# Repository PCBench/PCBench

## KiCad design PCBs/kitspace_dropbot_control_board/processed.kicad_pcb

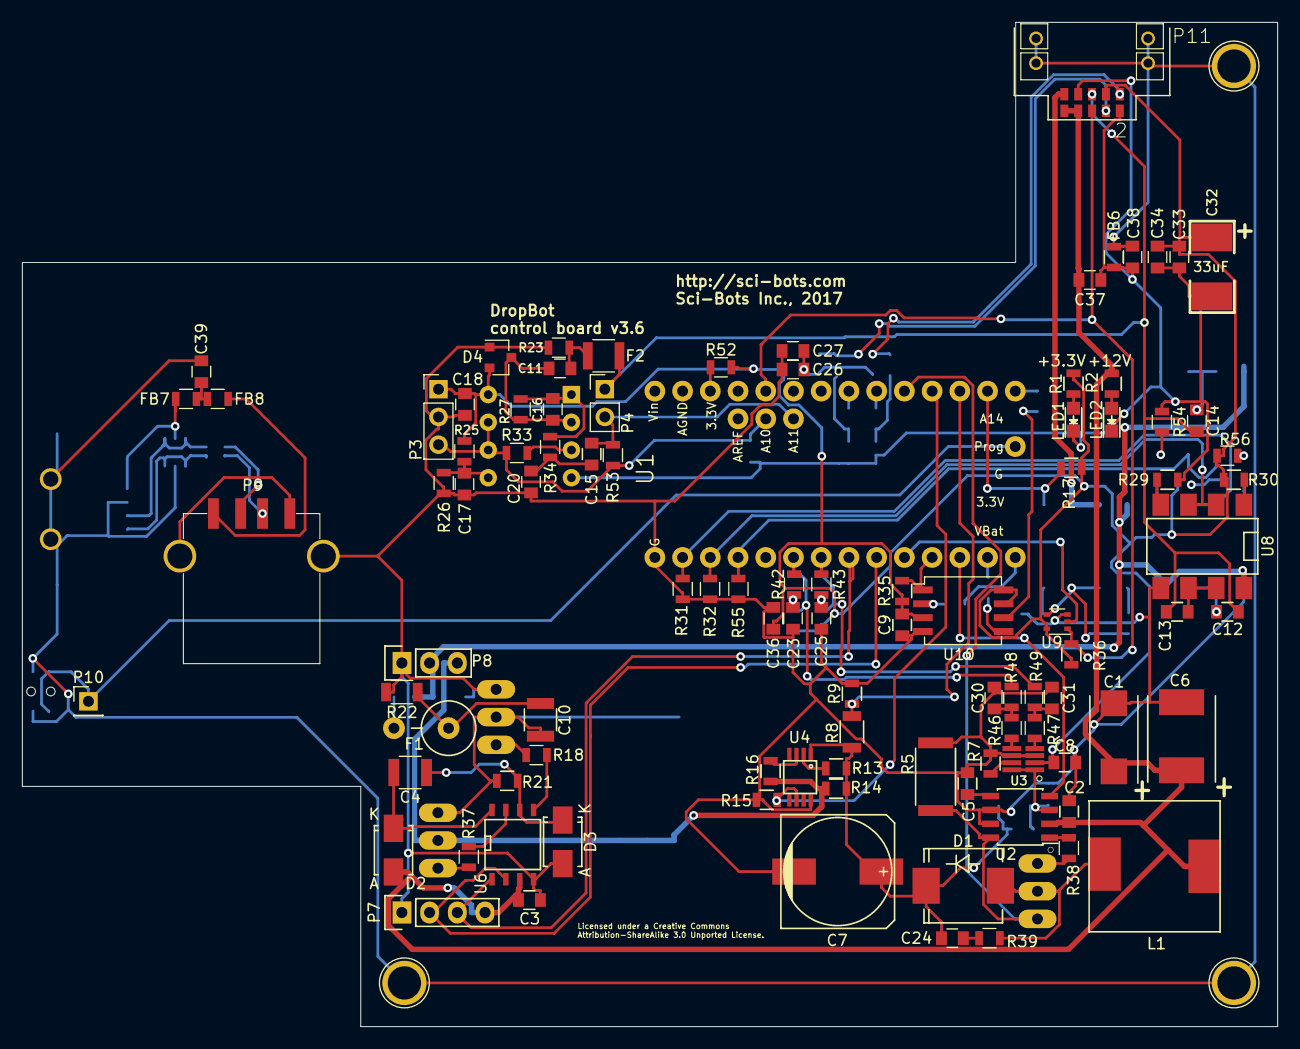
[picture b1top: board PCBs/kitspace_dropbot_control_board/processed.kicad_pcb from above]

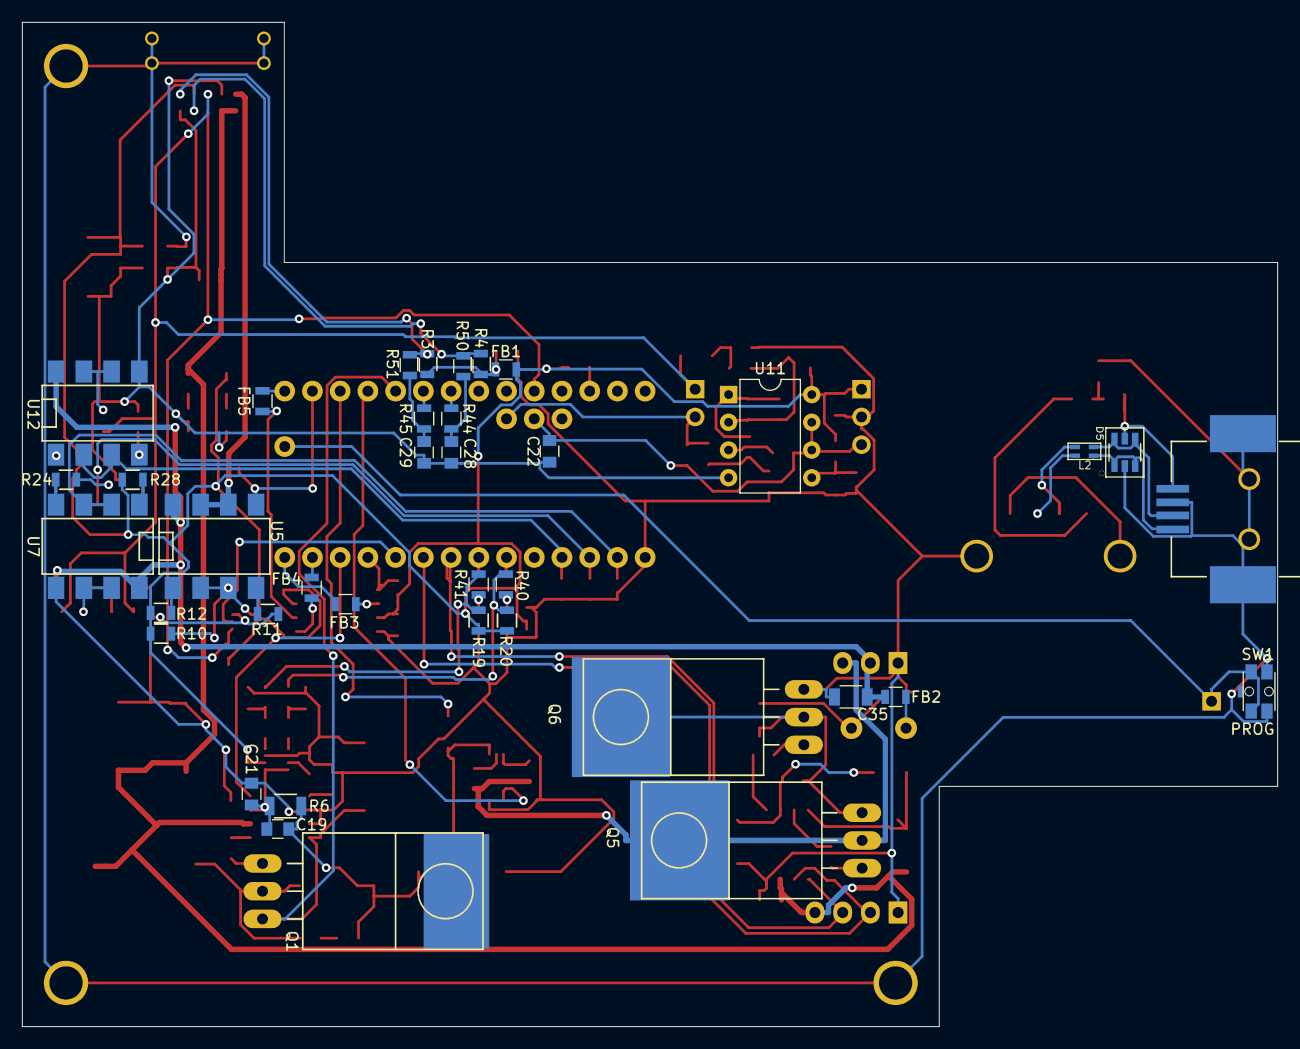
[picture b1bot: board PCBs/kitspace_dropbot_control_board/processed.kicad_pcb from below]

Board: 4 copper layers, 115.0 x 92.0 mm, 141 parts (38 on the bottom side), 94 nets.

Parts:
C1: 10uF; TantalC_SizeD_EIA-7343_Reflow
C2, C3, C5, C8, C9, C17, C18, C22, C26, C33, C36, C37, C38, C39: 0.1uF; C_0805
C4, C10: 100n,500V; C_1210
C6: 100uF; TantalC_SizeE_EIA-7360_Reflow
C7: 3.3uF,400V; c_elec_10x10
C11, C15: 1uF; C_0805
C12: 10pF; C_0805
C13, C19, C20, C21: 100pF; C_0805
C14: 470pF; C_0805
C16: 0.15uF; C_0805
C23, C25, C28, C29, C30, C31: 150pF; C_0805
C24: 1000pF; C_0805
C27, C34: 0.01uF; C_0805
C32: 33uF; SM2917
C35: C; C_1206
D1: 400V, 4A, <50ns; SMC_Standard
D2, D3: D; SMA_Standard
D4: BAV99; SOT-23
D5: WE-TVS_824015; wurth-WE-TVS_SOT23-6L
F1: PTC; Resistor_Vertical_RM5mm
F2: PTC 15mA; R_1210
FB1, FB2, FB3, FB4, FB5, FB6, FB7, FB8: FERRITE; R_0805
L1: 47uH,3.8A; SRR1210
L2: 90 Ohm@100MHz; wurth-WE-CNSW_0805
LED1: +3.3V; LED_0805
LED2: +12V; LED_0805
P1, P2, P5: CONN_01X01; 1pin
P3: CONN_01X03; Pin_Header_Straight_1x03_Pitch2.54mm
P4: CONN_01X02; Pin_Header_Straight_1x02_Pitch2.54mm
P6: USB_B; 1734346-1
P7: CONN_01X04; Pin_Header_Straight_1x04
P8: CONN_01X03; Pin_Header_Straight_1x03
P9: USB_A; AU-Y1006
P10: CONN_01X01; Pin_Header_Straight_1x01_Pitch2.54mm
P11: TFM-105-02-X-DH
Q1: STP33N65M2; TO-220_Neutral123_Horizontal_LargePads
Q5, Q6: IRF740BPBF; TO-220_Neutral123_Horizontal_LargePads
R1: 1k; R_0805
R2, R3, R4, R19, R20: 2k; R_0805
R5: 30m; R_2512
R6, R8, R22: 2M; R_1206
R7: 9.1k; R_0805
R9: 20k; R_0805
R10, R13, R31, R32, R34, R35, R36, R55: 5.1k; R_0805
R11, R12, R24, R28, R29, R30, R54, R56: 100; R_0805
R14: 1; R_0805
R15, R17: 51k; R_0805
R16, R27, R33: 100k; R_0805
R18, R21, R37, R38, R39: 10; R_0805
R23, R53: 1Meg; R_0805
R25: 10k; R_0805
R26: 2.2k; R_0805
R40, R41, R48, R49, R50, R51: 150; R_0805
R42, R43, R44, R45, R46, R47: 51; R_0805
R52: 0R; R_0805
SW1: PROG; PTS840_GK_SMTR_LFS
U1: Teensy_3.2; Teensy-3.2
U2: MAX1771; SOIC-8_3.9x4.9mm_Pitch1.27mm
U3: CAT5171; SOT-23-8
U4: HV7802; MSOP-8
U5, U7, U8, U12: DPST (2 Form A), 350V; DIP-8_SMD
U6: NCP5304; SOIC-8-N
U9: 74AHC1G32; SOT-353
U10: IS25LP064A-JBLE; SSO-8_5.2x5.2mm_Pitch1.27mm
U11: MCP6022; DIP-8_W7.62mm

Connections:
+0.6V: C22.2, P3.3, R33.1, R53.2, U1.34, U11.6, U11.7
+3V3: C8.2, C9.1, C18.1, C32.1, C33.2, C34.2, C36.2, D4.2, FB1.2, P3.1, P11.3, R1.1, R10.1, R12.1, R17.1, R19.2, R20.2, R25.1, R28.1, R30.1, R35.2, R36.2, R52.1, R56.1, U3.2, U9.5, U10.3, U10.7, U10.8, U11.8
+12V: C1.1, C2.2, C3.2, C6.1, C37.2, D2.2, L1.2, P7.4, P11.8, P11.10, R2.1, U2.2, U6.3
/USB pass-through/D+: L2.2, P9.3
/USB pass-through/D-: L2.3, P9.2
A0/SHORT_CHK: R17.2, U1.14, U5.5
A1/HV_FB: R8.1, R9.2, U1.15
A2/HV7802_CS: R15.2, U1.16, U4.6
A3/MAX1771_CS: Q1.3, R5.1, U1.17, U2.8
A11: C15.2, P4.2, R53.1, U1.33
CHASIS_GND: C38.1, C39.1, D5.2, FB6.2, P1.1, P2.1, P5.1, P6.4, P6.5, P11.G1, P11.G2, P11.G3, P11.G4, SW1.2
CUR_SENSE: C12.2, C13.2, C14.2, F2.2, P4.1, P11.5
D0: R31.1, U1.0, U7.2, U7.3
D1: R32.1, U1.1, U8.2, U8.3
D2: R55.1, U1.2, U12.2, U12.3
D4/SSDA: R20.1, R40.2, R48.1
D5/SSCL: R19.1, R41.2, R49.1
D6/DRIVER_LO: P7.3, U1.6, U6.1
D7/DRIVER_HI: P7.2, U1.7, U6.2
D8/OUTPUT_SELECT: U1.8, U9.2
D9/CS: R35.1, U1.9, U10.1
D10/SHDN: U1.10, U2.4
D11/M0SI: FB4.1, U10.5
D12/MISO: FB3.1, U1.12
D13/CLK: FB5.2, U10.6
GND: C1.2, C2.1, C3.1, C5.2, C6.2, C7.2, C8.1, C9.2, C17.2, C18.2, C20.1, C21.1, C22.1, C23.2, C25.1, C26.1, C27.1, C28.2, C29.1, C30.2, C31.1, C32.2, C33.1, C34.1, C35.1, C36.1, C37.1, C38.2, D3.2, D4.1, FB6.1, LED1.1, LED2.1, P3.2, P7.1, P8.1, P9.4, P9.5, P11.2, P11.7, Q6.3, R5.2, R7.2, R9.1, R11.1, R15.1, R22.2, R23.2, R24.1, R26.2, R29.1, R31.2, R32.2, R54.1, R55.2, U1.27, U2.6, U2.7, U3.3, U3.6, U4.8, U6.4, U7.5, U8.5, U9.3, U10.4, U11.4, U12.5
HV: P8.3, Q5.2, R14.1, R16.2
HVAC: C35.2, FB2.2, P8.2, U5.8, U7.8, U8.8, U12.8
HV_OE: P11.6, R36.1, U1.22, U9.1
unnamed: C4.1, D3.1, R21.2, U6.6
unnamed: C4.2, D2.1, U6.8
unnamed: C5.1, U2.5
unnamed: C10.1, Q5.3, Q6.2, R21.1
unnamed: C10.2, F1.1, R22.1
unnamed: C11.1, F2.1, R23.1
unnamed: C11.2, C16.2, D4.3, R27.2, U11.2
unnamed: C12.1, U7.6, U7.7
unnamed: C13.1, U8.6, U8.7
unnamed: C14.1, U12.6, U12.7
unnamed: C15.1, C20.2, R34.1
unnamed: C16.1, R27.1, R34.2, U11.1
unnamed: C17.1, R25.2, R26.1, U11.5
unnamed: C19.1, C21.2, R6.2, U2.3, U3.1, U3.8
unnamed: C7.1, C19.2, C24.1, D1.1, R6.1, R8.2, R13.1, R14.2, U4.1
unnamed: C23.1, R40.1, R42.2
unnamed: C24.2, R39.1
unnamed: C25.2, R41.1, R43.2
unnamed: C26.2, C27.2, FB1.1, R3.1, R4.1
unnamed: C28.1, R44.1, R50.2
unnamed: C29.2, R45.1, R51.2
unnamed: C30.1, R46.1, R48.2
unnamed: C31.2, R47.1, R49.2
unnamed: C39.2, FB7.2, FB8.1
unnamed: D1.2, L1.1, Q1.2, R39.2
unnamed: D5.1, D5.3, L2.1, P6.3
unnamed: D5.4, D5.6, L2.4, P6.2
unnamed: D5.5, FB7.1, P6.1
unnamed: F1.2, FB2.1
unnamed: FB3.2, U10.2
unnamed: FB4.2, U1.11
unnamed: FB5.1, U1.13
unnamed: FB8.2, P9.1
unnamed: LED1.2, R1.2
unnamed: LED2.2, R2.2
unnamed: Q1.1, R38.1
unnamed: Q5.1, R37.1
unnamed: Q6.1, R18.1
unnamed: R7.1, U3.7
unnamed: R10.2, U5.2, U5.3, U9.4
unnamed: R11.2, U5.4
unnamed: R12.2, U5.1
unnamed: R13.2, U4.2
unnamed: R16.1, U4.3
unnamed: R18.2, U6.5
unnamed: R24.2, U7.4
unnamed: R28.2, U7.1
unnamed: R29.2, U8.4
unnamed: R30.2, U8.1
unnamed: R33.2, U11.3
unnamed: R37.2, U6.7
unnamed: R38.2, U2.1
unnamed: R42.1, U1.4
unnamed: R43.1, U1.5
unnamed: R44.2, U1.19
unnamed: R45.2, U1.18
unnamed: R46.2, U3.5
unnamed: R47.2, U3.4
unnamed: R52.2, U1.24
unnamed: R54.2, U12.4
unnamed: R56.2, U12.1
PROG: P10.1, SW1.1, U1.29
SCL: P11.4, R4.2, R50.1
SDA: P11.1, R3.2, R51.1
VOUT: P11.9, U5.6, U5.7

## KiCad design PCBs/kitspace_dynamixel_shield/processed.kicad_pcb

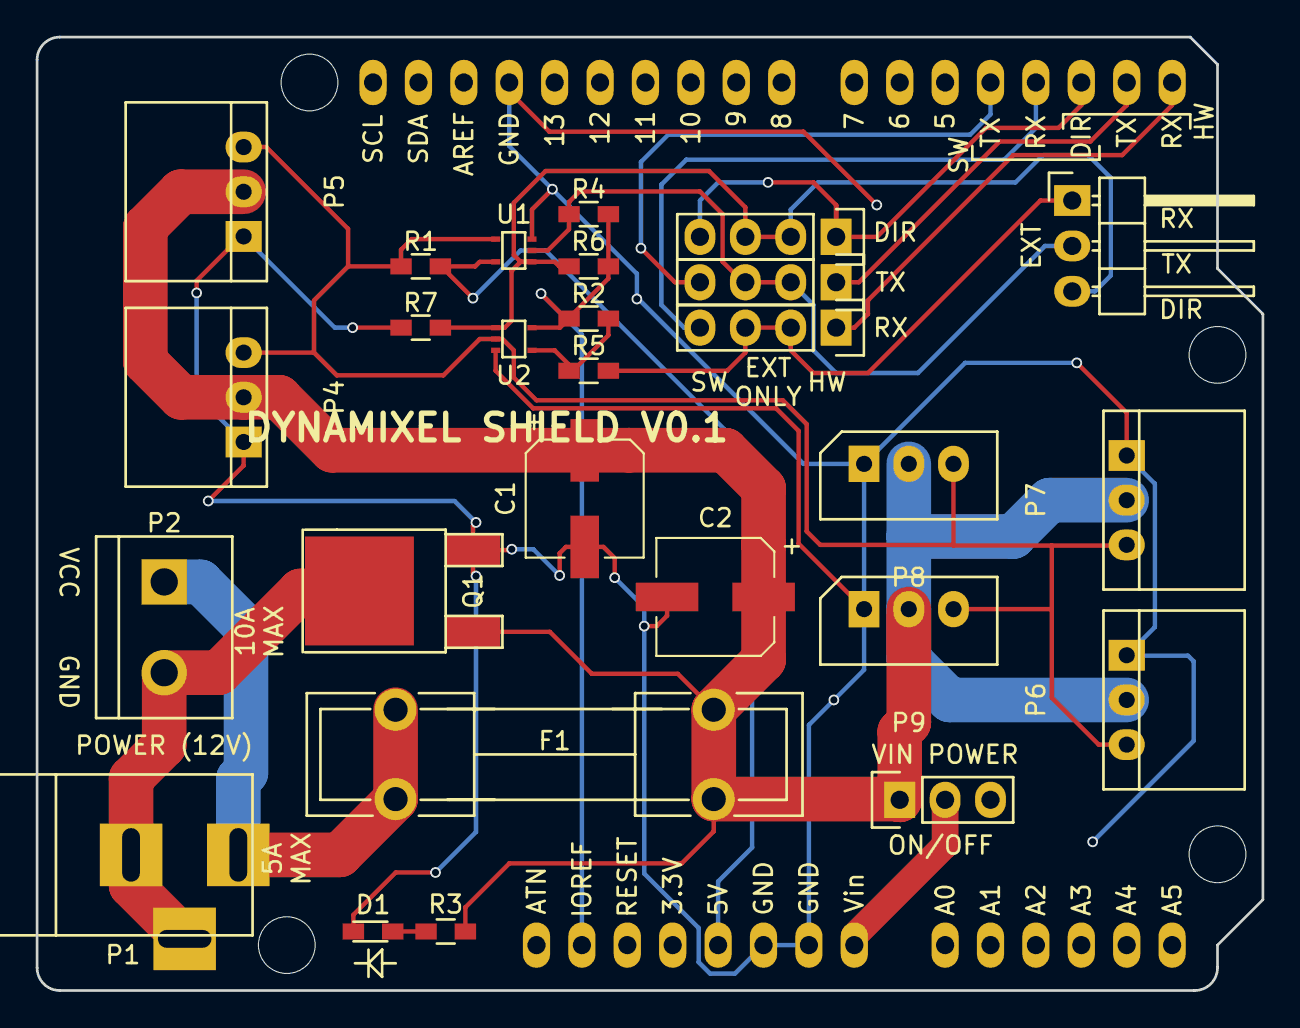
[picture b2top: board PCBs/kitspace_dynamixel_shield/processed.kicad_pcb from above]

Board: 2 copper layers, 68.6 x 53.3 mm, 28 parts (0 on the bottom side), 18 nets.

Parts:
C1, C2: 220uF; CP_Elec_6.3x7.7
D1: LED; LED_0603
F1: F_Small; Fuseholder5x20_horiz_lateral
JP1, JP2, JP3: JUMPER4; Pin_Header_Straight_1x04
JP4: JUMPER3; Pin_Header_Straight_1x03
P1: BARREL_JACK
P2: CONN_01X02; bornier2
P3: CONN_01X03; Pin_Header_Angled_1x03
P4, P5, P6, P7: CONN_01X03; Molex_spox_1x3_right
P8, P9: CONN_01X03; Molex_spox_1x3_straight
Q1: MOSFET_N; TO-252-2Lead
R1, R2, R3, R4, R6, R7: 10K; R_0603_HandSoldering
R5: 200; R_0603_HandSoldering
SHIELD1: ARDUINO_SHIELD; Arduino_shield_dynamixel
U1: 74AHCT1G126; SOT-353
U2: 74AHC1G125; SOT-353

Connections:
+5V: R1.1, SHIELD1.5V, U1.5
+12V: C1.1, C2.1, F1.2, JP4.1, P4.2, P5.2, P6.2, P7.2, P8.2, P9.2, Q1.1, R3.1
/ARDUINO_DIRECTION_PORT: JP1.1, JP1.4, SHIELD1.2
/DATA: P4.3, P5.3, P6.3, P7.3, P8.3, P9.3, R1.2, U1.4, U2.2
/DIRECTION_PORT: JP1.2, JP1.3, P3.3, R6.2, R7.1, U1.1, U2.1
/HW_RXD: JP3.1, SHIELD1.0
/HW_TXD: JP2.1, SHIELD1.1
/IOREF: R2.1, R4.1, R6.1, SHIELD1.IO_R, U2.5
/RXD: JP3.2, JP3.3, P3.1, R5.2
/SW_RXD: JP3.4, SHIELD1.3
/SW_TXD: JP2.4, SHIELD1.4
/TXD: JP2.2, JP2.3, P3.2, R4.2, U1.2
/VIN: JP4.2, SHIELD1.VIN
GND: C1.2, C2.2, D1.1, P4.1, P5.1, P6.1, P7.1, P8.1, P9.1, Q1.3, R7.2, SHIELD1.GND, U1.3, U2.3
unnamed: D1.2, R3.2
unnamed: F1.1, P1.1, P2.1
unnamed: P1.2, P1.3, P2.2, Q1.2
unnamed: R2.2, R5.1, U2.4

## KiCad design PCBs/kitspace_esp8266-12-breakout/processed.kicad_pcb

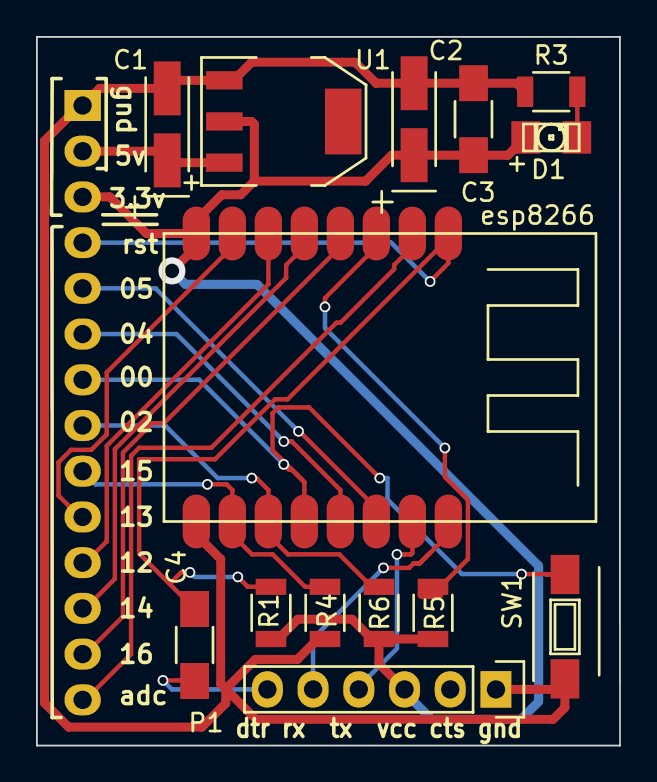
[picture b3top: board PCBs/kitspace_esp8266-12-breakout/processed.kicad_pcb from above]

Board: 2 copper layers, 32.4 x 39.4 mm, 15 parts (1 on the bottom side), 19 nets.

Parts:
C1, C2: 10uf; TantalC_SizeA_EIA-3216_HandSoldering
C3: 0.1uf; C_1206_HandSoldering
C4: 1uf; C_1206_HandSoldering
D1: LED; LED-1206
P1: ftdi; Pin_Header_Straight_1x06
P2: CONN_01X14; Pin_Header_Straight_1x14
R1, R4, R5, R6: 10k; R_1206
R3: 68r; R_1206
SW1: SW_PUSH; SW_SPST_FSMSM
U1: AP1117D33; SOT-223
esp8266: U2; esp8266-12

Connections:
+3V3: C2.1, C3.1, D1.2, P1.3, P2.3, R1.1, R4.1, R5.1, U1.2, esp8266.8
+5V: C1.1, P2.2, U1.3
/adc: P2.14, esp8266.2
/ch_pd: R5.2, esp8266.3
/gpio0: P2.7, SW1.1, esp8266.12
/gpio2: P2.8, R4.2, esp8266.11
/gpio4: P2.6, esp8266.13
/gpio5: P2.5, esp8266.14
/gpio12: P2.11, esp8266.6
/gpio13: P2.10, esp8266.7
/gpio14: P2.12, esp8266.5
/gpio15: P2.9, R6.1, esp8266.10
/gpio16: P2.13, esp8266.4
/reset: C4.2, P2.4, R1.2, esp8266.1
/rx: P1.4, esp8266.15
/tx: P1.5, esp8266.16
GND: C1.2, C2.2, C3.2, P1.1, P2.1, R3.2, R6.2, SW1.2, U1.1, esp8266.9
unnamed: C4.1, P1.6
unnamed: D1.1, R3.1

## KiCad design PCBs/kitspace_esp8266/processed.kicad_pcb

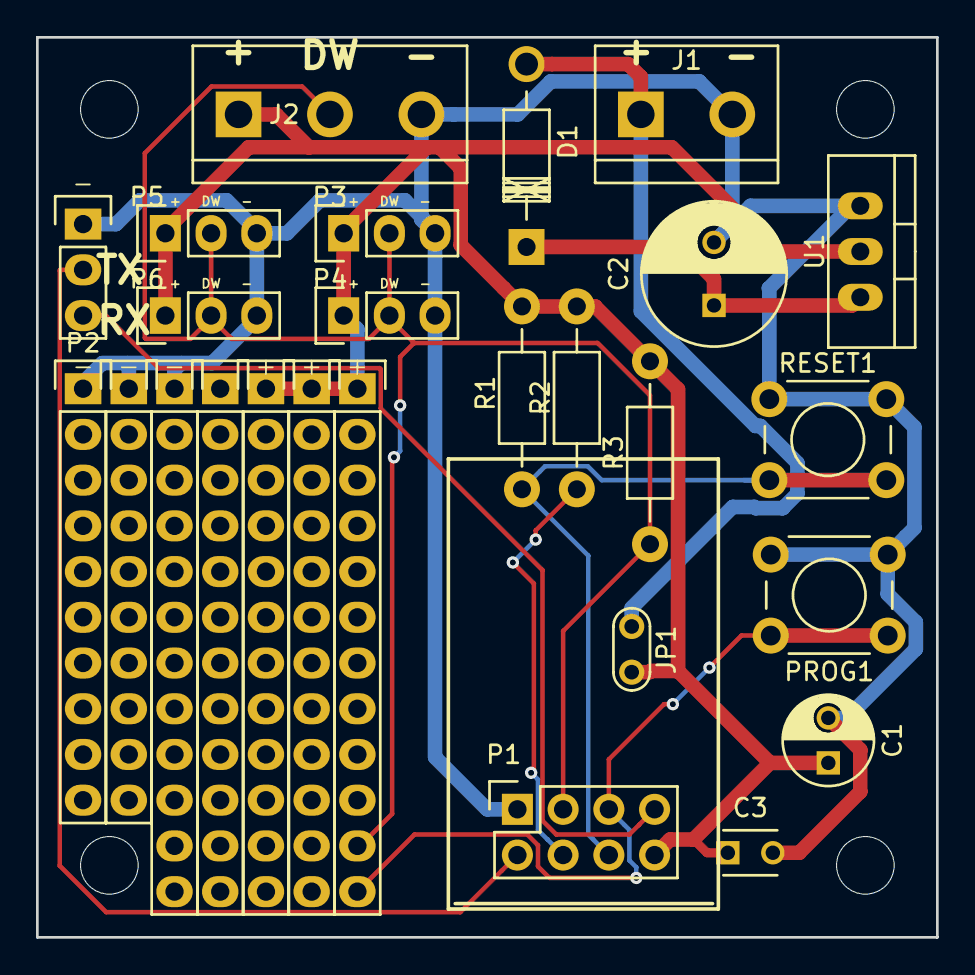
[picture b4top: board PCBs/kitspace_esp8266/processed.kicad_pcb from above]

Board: 2 copper layers, 50.0 x 50.0 mm, 19 parts (0 on the bottom side), 10 nets.

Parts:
C1: 10uf; C_Radial_D5_L6_P2.5
C2: 100uf; C_Radial_D8_L11.5_P3.5
C3: C_Small; C_Disc_D3_P2.5
D1: D; Diode_DO-41_SOD81_Horizontal_RM10
J1: Screw_Terminal_1x02; bornier2
J2: Screw_Terminal_1x03; bornier3
JP1: JUMPER_NO_Small; TEST_POINT_2PADS
P1: CONN_02X04; Socket_Strip_Straight_2x04
P2: CONN_01X03; Pin_Header_Straight_1x03
P3, P4, P5, P6: CONN_01X03; Socket_Strip_Straight_1x03
PROG1: SW_PUSH; SW_PUSH_6mm
R1, R2: 2.2k; Resistor_Horizontal_RM10mm
R3: 4.7k; Resistor_Horizontal_RM10mm
RESET1: SW_PUSH; SW_PUSH_6mm
U1: LD1117S33TR; TO-220_Neutral123_Vertical

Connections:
+3V3: C1.1, C3.1, J2.1, JP1.2, P1.8, P3.1, P4.1, P5.1, P6.1, R1.2, R2.2, R3.1, U1.2
/CH_PD: P1.4, R2.1
/PROG: P1.5, PROG1.1
/RST: P1.6, R1.1, RESET1.2
DW: J2.2, P1.3, P3.2, P4.2, P5.2, P6.2, R3.2
GND: C1.2, C2.2, C3.2, J1.2, J2.3, P1.1, P2.1, P3.3, P4.3, P5.3, P6.3, PROG1.2, RESET1.1, U1.1
RX: P1.7, P2.3
TX: P1.2, P2.2
VCC: D1.2, J1.1, JP1.1
VDD: C2.1, D1.1, U1.3

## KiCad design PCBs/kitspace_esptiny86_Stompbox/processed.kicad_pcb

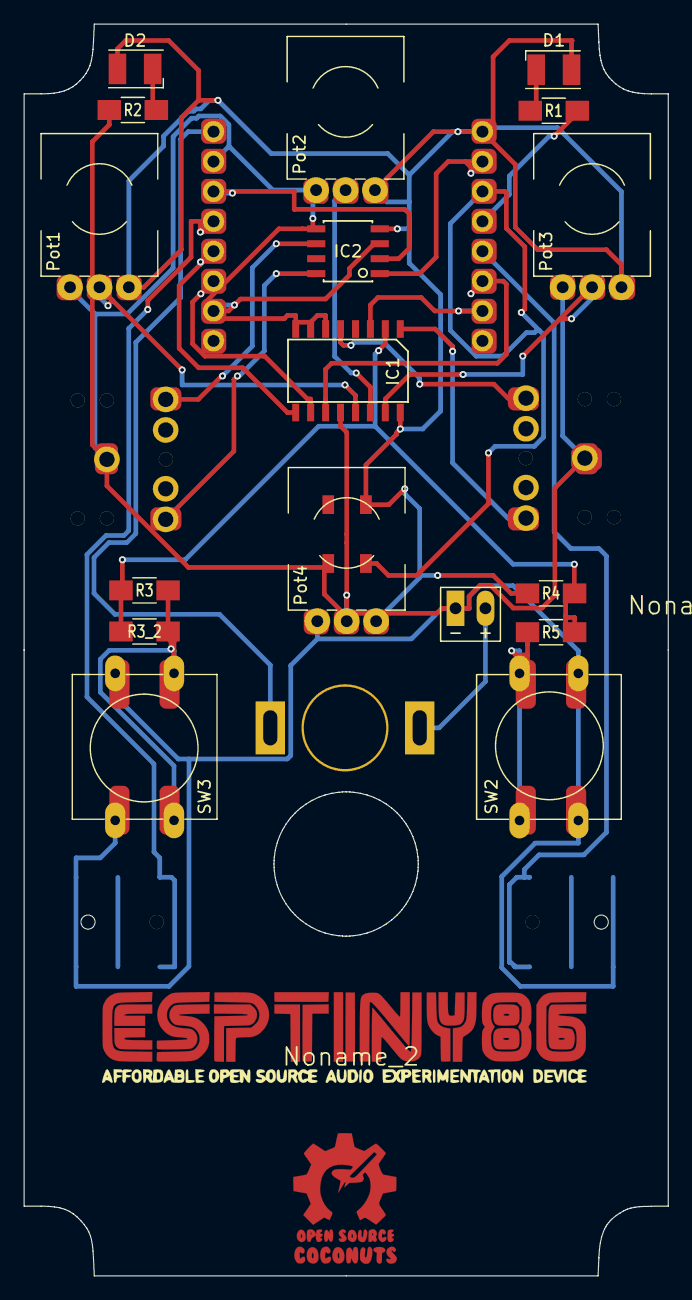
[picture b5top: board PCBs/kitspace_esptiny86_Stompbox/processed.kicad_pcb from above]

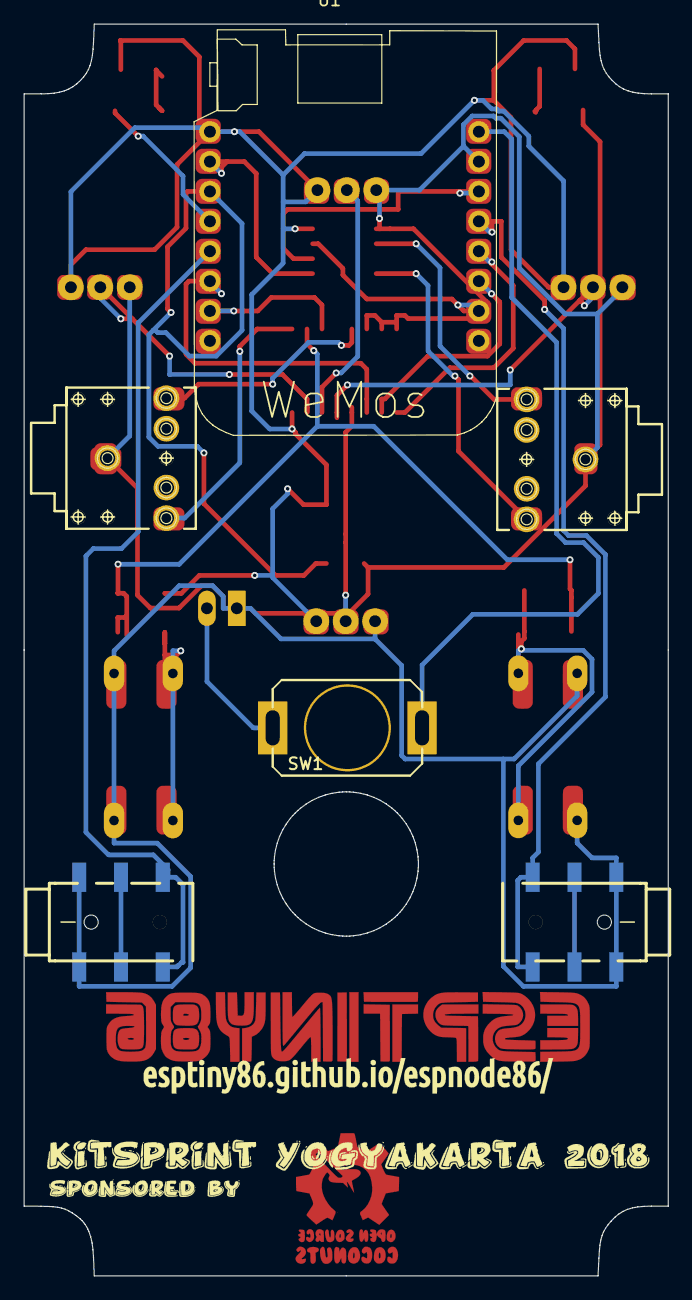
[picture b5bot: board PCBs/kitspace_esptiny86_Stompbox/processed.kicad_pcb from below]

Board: 2 copper layers, 54.8 x 106.4 mm, 28 parts (6 on the bottom side), 28 nets.

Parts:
Coconut: LOGO; Coconut_Logo_small_Mask
Coconut_2: LOGO; Coconut_Logo_small
D1, D2: LED; TopLED_2835
IC1: 4051; 4xxx_SOIC-16W_Pitch1.27mm
IC2: DAC7513_DCN; SOIC-8_3.9x4.9mm_Pitch1.27mm
J1: Bat_EXT; Bat_connector+-
Jack1, Jack3: JACK_TRS_6PINS; AUDIO-Jack_3.5mm_5Pin
Jack2, Jack4: JACK_TRS_6PINS; AUDIO-JACK-3.5mm_SMD
NEO8: LED_SK6813; Mixtape_NEO_WS2812B
Noname_1: StompBox_EdgesPCB
Noname_2: ESPTINY_logo
Pot1: 10k_big; ESP-Stomp_Pot_Alps
Pot2, Pot3, Pot4: 10k; ESP-Stomp_Pot_Alps
R1, R2: R; R_1206_Mixtape_Silk
R3, R3_2: 22k; R_1206_Mixtape_Silk
R4, R5: 10k; R_1206_Mixtape_Silk
SW1: SW_SPST; Push_SWITCH_hole
SW2, SW3: SW_Push; SW_PUSH-12mm_3D
U1: WeMos_mini; WeMOS_ESP

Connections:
+3V3: D1.2, D2.2, IC1.16, IC2.4, NEO8.1, Pot1.1, Pot2.1, Pot3.1, Pot4.1, R4.1, U1.16
+5V: SW1.2, U1.1
+BATT: J1.1, SW1.1
/PDS: IC2.3, U1.7
Buttons: IC1.2, R3.2, R3_2.2, R4.2, R5.2
CV1: IC1.1, Jack3.2
CV2: IC1.5, Jack3.3
D3: Jack2.2, U1.4
D5: Jack4.2, U1.12
GND: IC1.6, IC1.7, IC1.8, IC2.5, J1.2, Jack1.1, Jack2.1, Jack3.1, Jack4.1, NEO8.3, Pot1.3, Pot2.3, Pot3.3, Pot4.3, R2.1, SW2.2, SW3.2, U1.2
L-Out: IC2.6, Jack1.3
Led1_pulldown: R1.2, U1.13
NEO-Pixel: NEO8.4, U1.14
unnamed: D1.1, R1.1
unnamed: D2.1, R2.2
unnamed: IC1.3, U1.10
unnamed: IC1.9, U1.5
unnamed: IC1.10, U1.6
unnamed: IC1.11, U1.11
unnamed: IC2.1, U1.15
unnamed: IC2.2, U1.3
unnamed: R3.1, R3_2.1, SW3.1
unnamed: R5.1, SW2.1
Pot1: IC1.13, Pot1.2
Pot2: IC1.14, Pot2.2
Pot3: IC1.15, Pot3.2
Pot4: IC1.12, Pot4.2
R-Out: IC2.8, Jack1.2

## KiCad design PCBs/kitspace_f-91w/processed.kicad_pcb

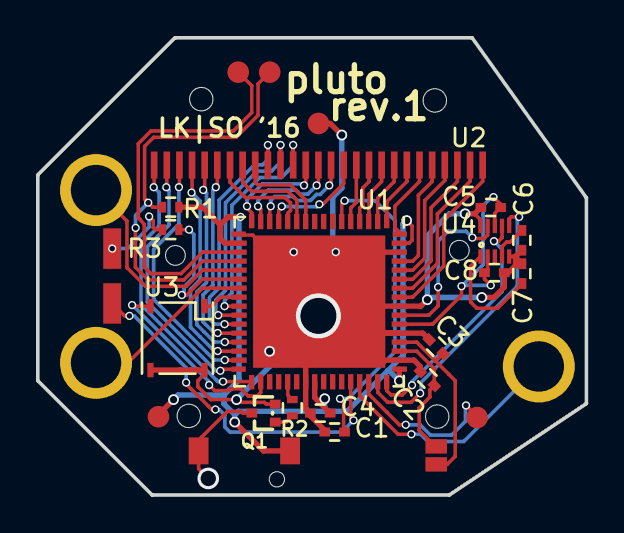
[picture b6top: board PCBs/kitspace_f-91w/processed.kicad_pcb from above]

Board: 2 copper layers, 30.5 x 25.4 mm, 37 parts (0 on the bottom side), 52 nets.

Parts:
C1: 4.7u; C_0402
C2, C3: 22p; C_0402
C4, C5, C6, C7, C8: 100n; C_0402
MH1, MH2, MH3, MH4, MH5, MH6, MH7: 1pin
P1, P2, P3, P4, P5, P6, P7, P8, P9, P10, P11, P13, P14, P15: CONN_01X01; 1pin
Q1: BC846; SOT416
R1, R3: 10k; R_0402
R2: 47k; R_0402
U1: MSP430FR6972; QFN-64-1EP_9x9mm_Pitch0.5mm
U2: LCD-F-91W
U3: TSOP57xxx
U4: MAG3110; DFN-10-1EP_2x2mm_Pitch0.4mm

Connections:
/BUZ: P9.1, Q1.3
/B_ALARM: P7.1, U1.45
/B_LIGHT: P5.1, U1.21
/B_MODE: P6.1, U1.23
/INT1: U1.55, U4.9
/IR: U1.24, U3.1
/IR_PWR: U1.34, U3.5
/LCD_COM1: U1.12, U2.7
/LCD_COM2: U1.11, U2.8
/LCD_COM3: U1.10, U2.9
/LCD_SEG1: U1.33, U2.1
/LCD_SEG2: U1.32, U2.2
/LCD_SEG3: U1.31, U2.3
/LCD_SEG4: U1.30, U2.4
/LCD_SEG5: U1.29, U2.5
/LCD_SEG6: U1.28, U2.6
/LCD_SEG7: U1.27, U2.10
/LCD_SEG8: U1.26, U2.11
/LCD_SEG9: U1.25, U2.12
/LCD_SEG10: U1.16, U2.13
/LCD_SEG11: U1.15, U2.14
/LCD_SEG12: U1.14, U2.15
/LCD_SEG13: U1.13, U2.16
/LCD_SEG14: U1.5, U2.17
/LCD_SEG15: U1.4, U2.18
/LCD_SEG16: U1.3, U2.19
/LCD_SEG17: U1.2, U2.20
/LCD_SEG18: U1.1, U2.21
/LCD_SEG19: U1.64, U2.22
/LCD_SEG20: U1.61, U2.23
/LCD_SEG21: U1.60, U2.24
/LCD_SEG22: U1.59, U2.25
/LCD_SEG23: U1.58, U2.26
/LCD_SEG24: U1.57, U2.27
/LED_1: P11.1, U1.44
/LED_2: R3.2, U1.22
/MAG_PWR: C5.2, C8.1, U1.54, U4.2, U4.8
/Q-1: C2.1, P1.1, U1.51
/Q-2: C3.1, P2.1, U1.52
/SCL: U1.48, U4.7
/SDA: U1.47, U4.6
GND: C1.2, C2.2, C3.2, C4.2, C5.1, C6.2, C7.2, C8.2, P13.1, Q1.2, U1.17, U1.39, U1.50, U1.53, U1.56, U1.62, U1.65, U3.6, U4.5, U4.10
unnamed: C1.1, U1.6
unnamed: C6.1, U4.4
unnamed: C7.1, U4.1
unnamed: P3.1, U1.19
unnamed: P4.1, R1.2, U1.20
unnamed: P10.1, R3.1
unnamed: P15.1, U1.46
unnamed: Q1.1, R2.2
unnamed: R2.1, U1.37
VCC: C4.1, P8.1, P14.1, R1.1, U1.18, U1.40, U1.49, U1.63

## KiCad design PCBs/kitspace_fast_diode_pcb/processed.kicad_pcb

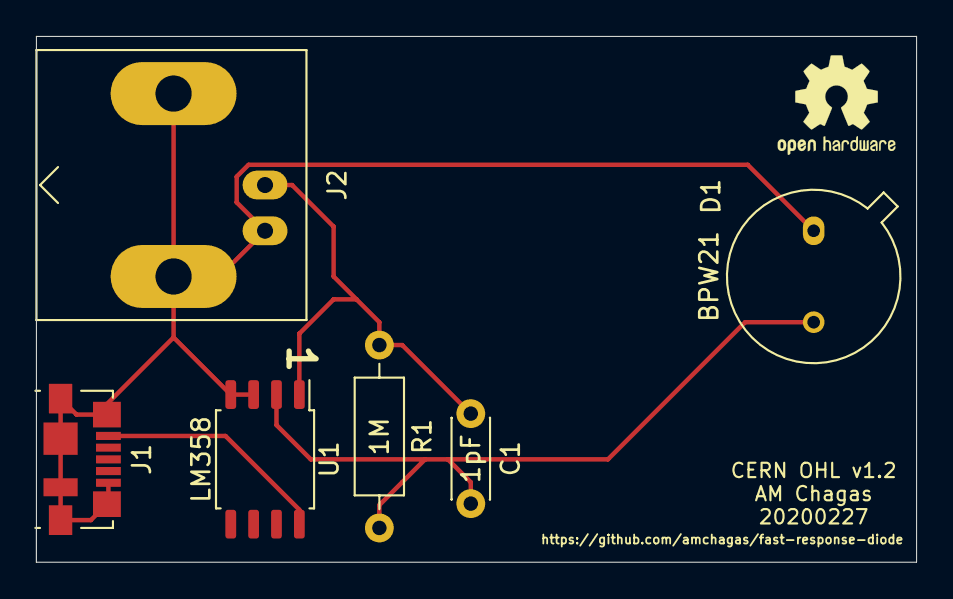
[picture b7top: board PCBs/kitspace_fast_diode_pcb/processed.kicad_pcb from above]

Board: 2 copper layers, 48.9 x 29.2 mm, 6 parts (0 on the bottom side), 4 nets.

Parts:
C1: 1pF; C_Disc_D4.3mm_W1.9mm_P5.00mm
D1: BPW21; TO-5-2_Window
J1: USB_B_Micro; USB_Micro-B_Molex_47346-0001
J2: Conn_Coaxial; BNC_Amphenol_B6252HB-NPP3G-50_Horizontal
R1: 1M; R_Axial_DIN0207_L6.3mm_D2.5mm_P10.16mm_Horizontal
U1: LM358; SOIC-8_5.23x5.23mm_P1.27mm

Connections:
+5V: J1.1, U1.8
/BNC+: C1.1, J2.1, R1.1, U1.1
GNDREF: D1.1, J1.5, J1.6, J2.2, U1.3, U1.4
unnamed: C1.2, D1.2, R1.2, U1.2

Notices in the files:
PCBs/kitspace_dropbot_control_board/processed.kicad_pcb:
Licensed under a Creative Commons
Attribution-ShareAlike 3.0 Unported License.
PCBs/kitspace_fast_diode_pcb/processed.kicad_pcb:
CERN OHL v1.2
